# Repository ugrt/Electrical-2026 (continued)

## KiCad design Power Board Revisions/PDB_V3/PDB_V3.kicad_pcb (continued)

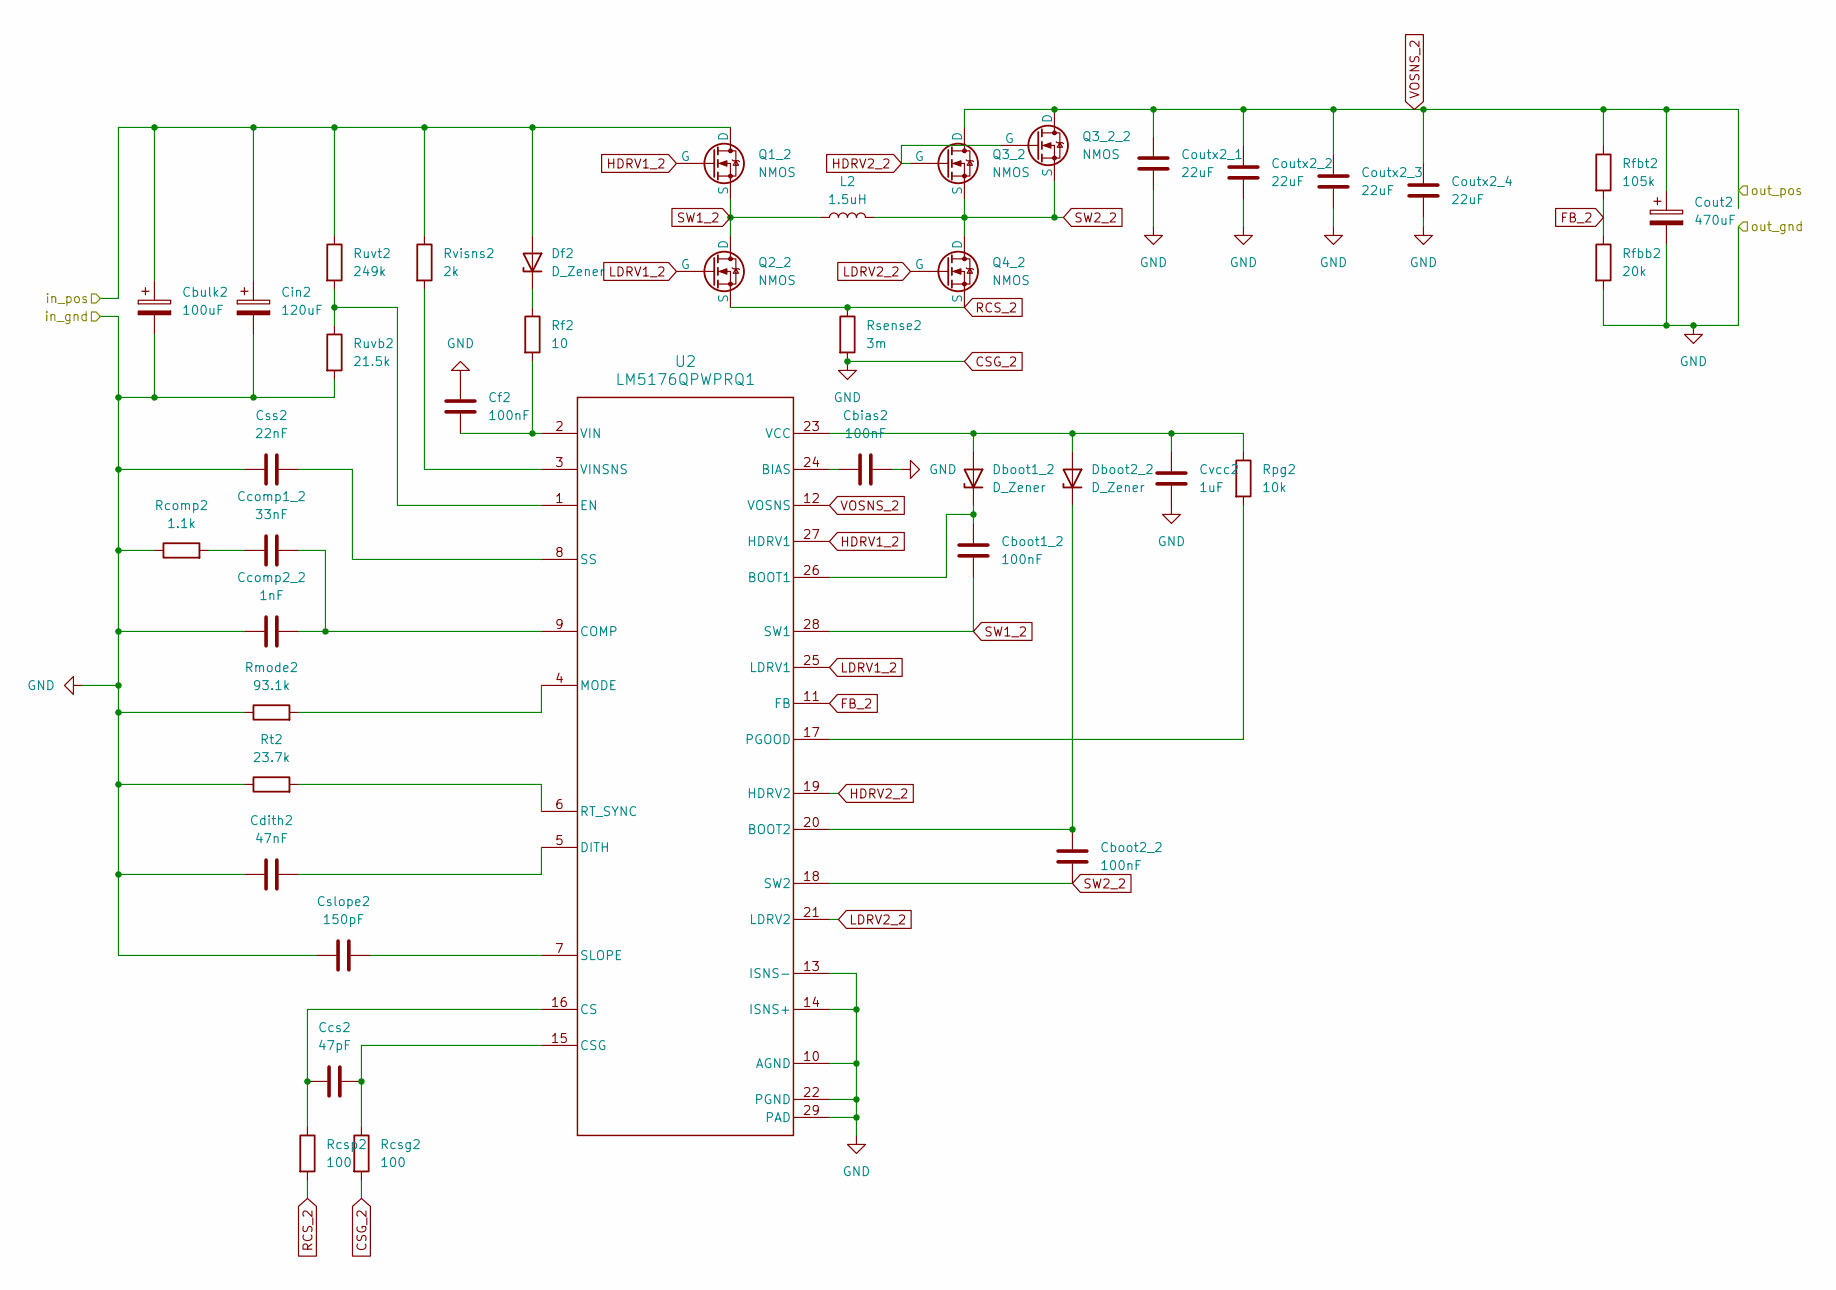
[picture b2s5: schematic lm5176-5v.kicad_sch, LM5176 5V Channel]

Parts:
Cbias2: 100nF; C_1206_3216Metric_Pad1.33x1.80mm_HandSolder; DigiKey_Part_Number 1276-3083-1-ND
Cboot1_2, Cboot2_2: 100nF; C_1206_3216Metric_Pad1.33x1.80mm_HandSolder; DigiKey_Part_Number 1276-3083-1-ND
Cbulk2: 100uF; CP_Radial_D10.0mm_P5.00mm; DigiKey_Part_Number P10343-ND
Ccomp1_2: 33nF; C_1206_3216Metric_Pad1.33x1.80mm_HandSolder; DigiKey_Part_Number 1276-3159-1-ND
Ccomp2_2: 1nF; C_1206_3216Metric_Pad1.33x1.80mm_HandSolder; DigiKey_Part_Number 1276-3070-1-ND
Ccs2: 47pF; C_1206_3216Metric_Pad1.33x1.80mm_HandSolder; DigiKey_Part_Number 1276-3270-1-ND
Cdith2: 47nF; C_1206_3216Metric_Pad1.33x1.80mm_HandSolder; DigiKey_Part_Number 1276-1149-1-ND
Cf2: 100nF; C_1206_3216Metric_Pad1.33x1.80mm_HandSolder; DigiKey_Part_Number KTS251B104K31N0T00
Cin2: 120uF; CP_Radial_D10.0mm_P5.00mm; DigiKey_Part_Number 10-EEU-FC1H121BCT-ND
Cout2: 470uF; CP_Radial_D10.0mm_P5.00mm; DigiKey_Part_Number 10-ECA-1HM471BCT-ND
Coutx2_1, Coutx2_2, Coutx2_3, Coutx2_4: 22uF; C_1206_3216Metric_Pad1.33x1.80mm_HandSolder; DigiKey_Part_Number 1276-3300-1-ND
Cslope2: 150pF; C_1206_3216Metric_Pad1.33x1.80mm_HandSolder; DigiKey_Part_Number 1276-CL31C151JHF1PNECT-ND
Css2: 22nF; C_1206_3216Metric_Pad1.33x1.80mm_HandSolder; DigiKey_Part_Number 1276-CL31B223KEFXPNECT-ND
Cvcc2: 1uF; C_1206_3216Metric_Pad1.33x1.80mm_HandSolder; DigiKey_Part_Number 1276-3093-1-ND
Dboot1_2, Dboot2_2: D_Zener; D_SOD-123F; DigiKey_Part_Number B260S1F-7DICT-ND
Df2: D_Zener; D_SOD-123F; DigiKey_Part_Number B260S1F-7DICT-ND
L2: 1.5uH; WE-HCM_1411
Q1_2, Q2_2, Q3_2, Q3_2_2, Q4_2: NMOS; IAUCN04S7L019
Rcomp2: 1.1k; R_1206_3216Metric_Pad1.30x1.75mm_HandSolder
Rcsg2: 100; R_1206_3216Metric_Pad1.30x1.75mm_HandSolder
Rcsp2: 100; R_1206_3216Metric_Pad1.30x1.75mm_HandSolder
Rf2: 10; R_1206_3216Metric_Pad1.30x1.75mm_HandSolder
Rfbb2: 20k; R_1206_3216Metric_Pad1.30x1.75mm_HandSolder
Rfbt2: 105k; R_1206_3216Metric_Pad1.30x1.75mm_HandSolder
Rmode2: 93.1k; R_1206_3216Metric_Pad1.30x1.75mm_HandSolder
Rpg2: 10k; R_1206_3216Metric_Pad1.30x1.75mm_HandSolder
Rsense2: 3m; WSLP2512-3L000
Rt2: 23.7k; R_1206_3216Metric_Pad1.30x1.75mm_HandSolder
Ruvb2: 21.5k; R_1206_3216Metric_Pad1.30x1.75mm_HandSolder
Ruvt2: 249k; R_1206_3216Metric_Pad1.30x1.75mm_HandSolder
Rvisns2: 2k; R_1206_3216Metric_Pad1.30x1.75mm_HandSolder
U2: LM5176QPWPRQ1; LM5176QPWPRQ1_N

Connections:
FB_2: Rfbb2.1, Rfbt2.2, U2.11 (FB)
GND: Cbias2.2, Cbulk2.2, Ccomp2_2.1, Cdith2.2, Cf2.1, Cin2.2, Cout2.2, Coutx2_1.2, Coutx2_2.2, Coutx2_3.2, Coutx2_4.2, Cslope2.1, Css2.1, Cvcc2.2, Rcomp2.1, Rcsg2.2, Rfbb2.2, Rmode2.1, Rsense2.2, Rt2.1, Ruvb2.2, U2.10 (AGND), U2.13 (ISNS-), U2.14 (ISNS+), U2.22 (PGND), U2.29 (PAD); also elsewhere on the board
HDRV1_2: Q1_2.2 (G), U2.27 (HDRV1)
HDRV2_2: Q3_2.2 (G), Q3_2_2.2 (G), U2.19 (HDRV2)
LDRV1_2: Q2_2.2 (G), U2.25 (LDRV1)
LDRV2_2: Q4_2.2 (G), U2.21 (LDRV2)
unnamed: Ccomp1_2.1, Rcomp2.2
unnamed: Cvcc2.1, Dboot1_2.2 (A), Dboot2_2.2 (A), Rpg2.1, U2.23 (VCC)
unnamed: Cboot1_2.1, Dboot1_2.1 (K), U2.26 (BOOT1)
unnamed: Cboot2_2.1, Dboot2_2.1 (K), U2.20 (BOOT2)
unnamed: Df2.1 (K), Rf2.1
unnamed: Cbias2.1, U2.24 (BIAS)
unnamed: Ccomp1_2.2, Ccomp2_2.2, U2.9 (COMP)
unnamed: Ccs2.1, Rcsp2.1, U2.16 (CS)
unnamed: Ccs2.2, Rcsg2.1, U2.15 (CSG)
unnamed: Cdith2.1, U2.5 (DITH)
unnamed: Ruvb2.1, Ruvt2.2, U2.1 (EN)
unnamed: Rmode2.2, U2.4 (MODE)
unnamed: Rpg2.2, U2.17 (PGOOD)
unnamed: Rt2.2, U2.6 (RT_SYNC)
unnamed: Cslope2.2, U2.7 (SLOPE)
unnamed: Css2.2, U2.8 (SS)
unnamed: Cf2.2, Rf2.2, U2.2 (VIN)
unnamed: Rvisns2.2, U2.3 (VINSNS)
RCS_2: Q2_2.3 (S), Q4_2.3 (S), Rcsp2.2, Rsense2.1
SW1_2: Cboot1_2.2, L2.1, Q1_2.3 (S), Q2_2.1 (D), U2.28 (SW1)
SW2_2: Cboot2_2.2, L2.2, Q3_2.3 (S), Q3_2_2.3 (S), Q4_2.1 (D), U2.18 (SW2)
VCC: Cbulk2.1, Cin2.1, Df2.2 (A), Q1_2.1 (D), Ruvt2.1, Rvisns2.1; also elsewhere on the board
VOSNS_2: Cout2.1, Coutx2_1.1, Coutx2_2.1, Coutx2_3.1, Coutx2_4.1, Q3_2.1 (D), Q3_2_2.1 (D), Rfbt2.1, U2.12 (VOSNS); also elsewhere on the board

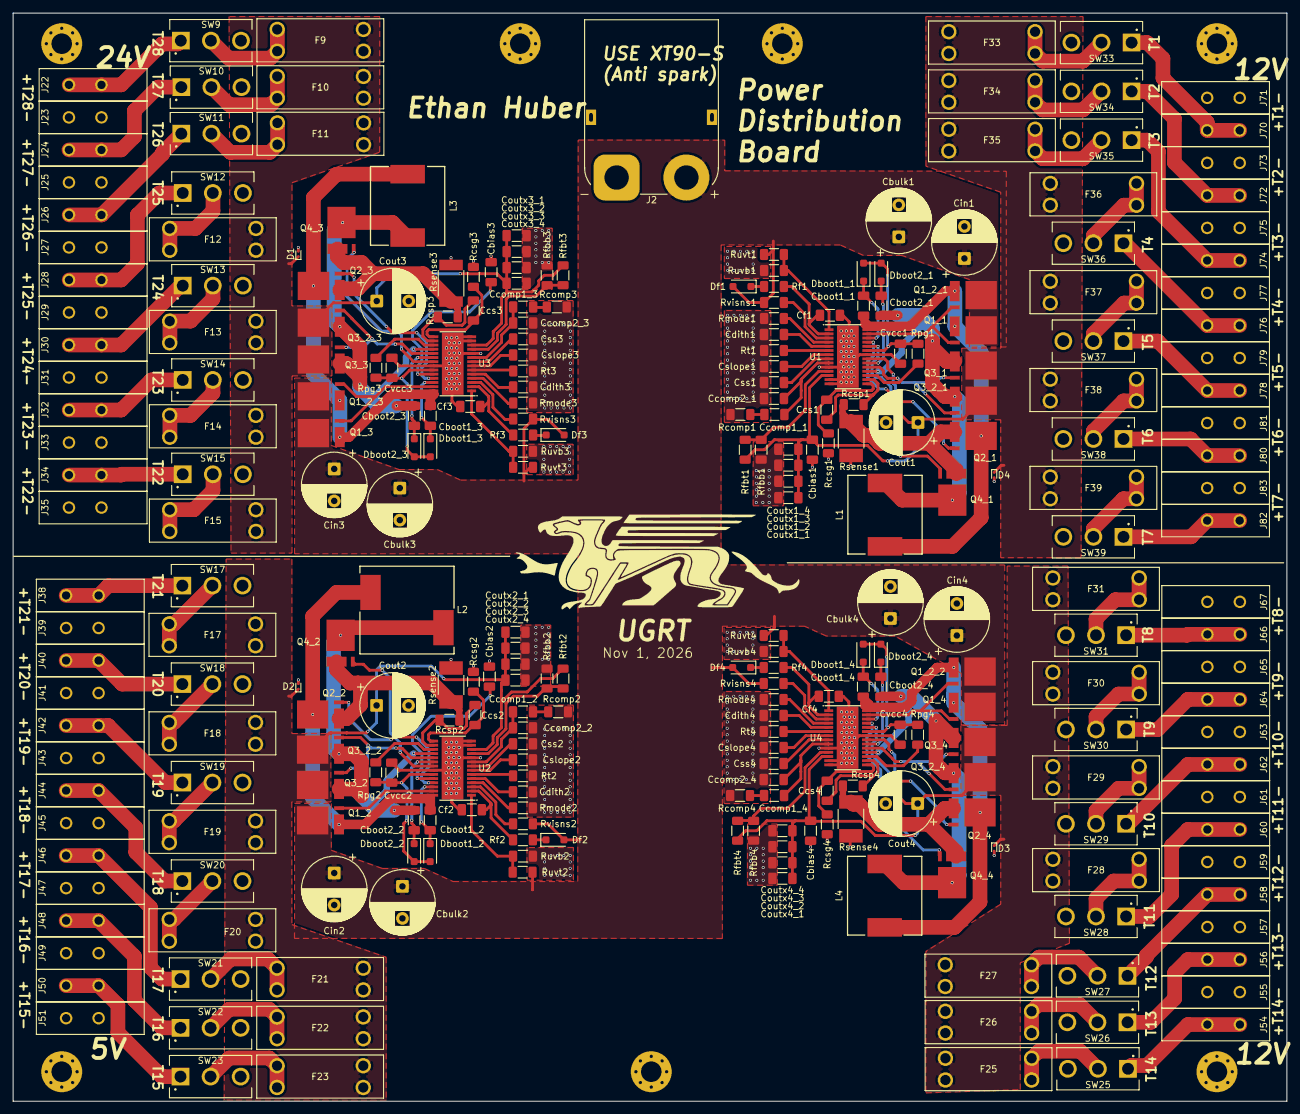
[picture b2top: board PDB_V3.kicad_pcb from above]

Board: 2 copper layers, 199.0 x 170.0 mm, 291 parts (0 on the bottom side), 164 nets.

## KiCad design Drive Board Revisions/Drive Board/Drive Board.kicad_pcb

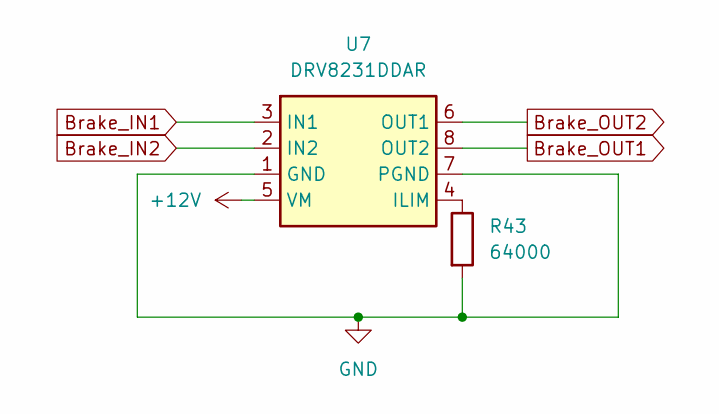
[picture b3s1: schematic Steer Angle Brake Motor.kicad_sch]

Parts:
R43: 64000; R_0603_1608Metric_Pad0.98x0.95mm_HandSolder
U7: DRV8231DDAR; Texas_HTSOP-8-1EP_3.9x4.9mm_P1.27mm_EP2.95x4.9mm_Mask2.4x3.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

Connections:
+12V: U7.5 (VM); also elsewhere on the board
Brake_IN1: U7.3 (IN1); also elsewhere on the board
Brake_IN2: U7.2 (IN2); also elsewhere on the board
Brake_OUT1: U7.8 (OUT2); also elsewhere on the board
Brake_OUT2: U7.6 (OUT1); also elsewhere on the board
GND: R43.2, U7.1 (GND), U7.7 (PGND); also elsewhere on the board
unnamed: R43.1, U7.4 (ILIM)

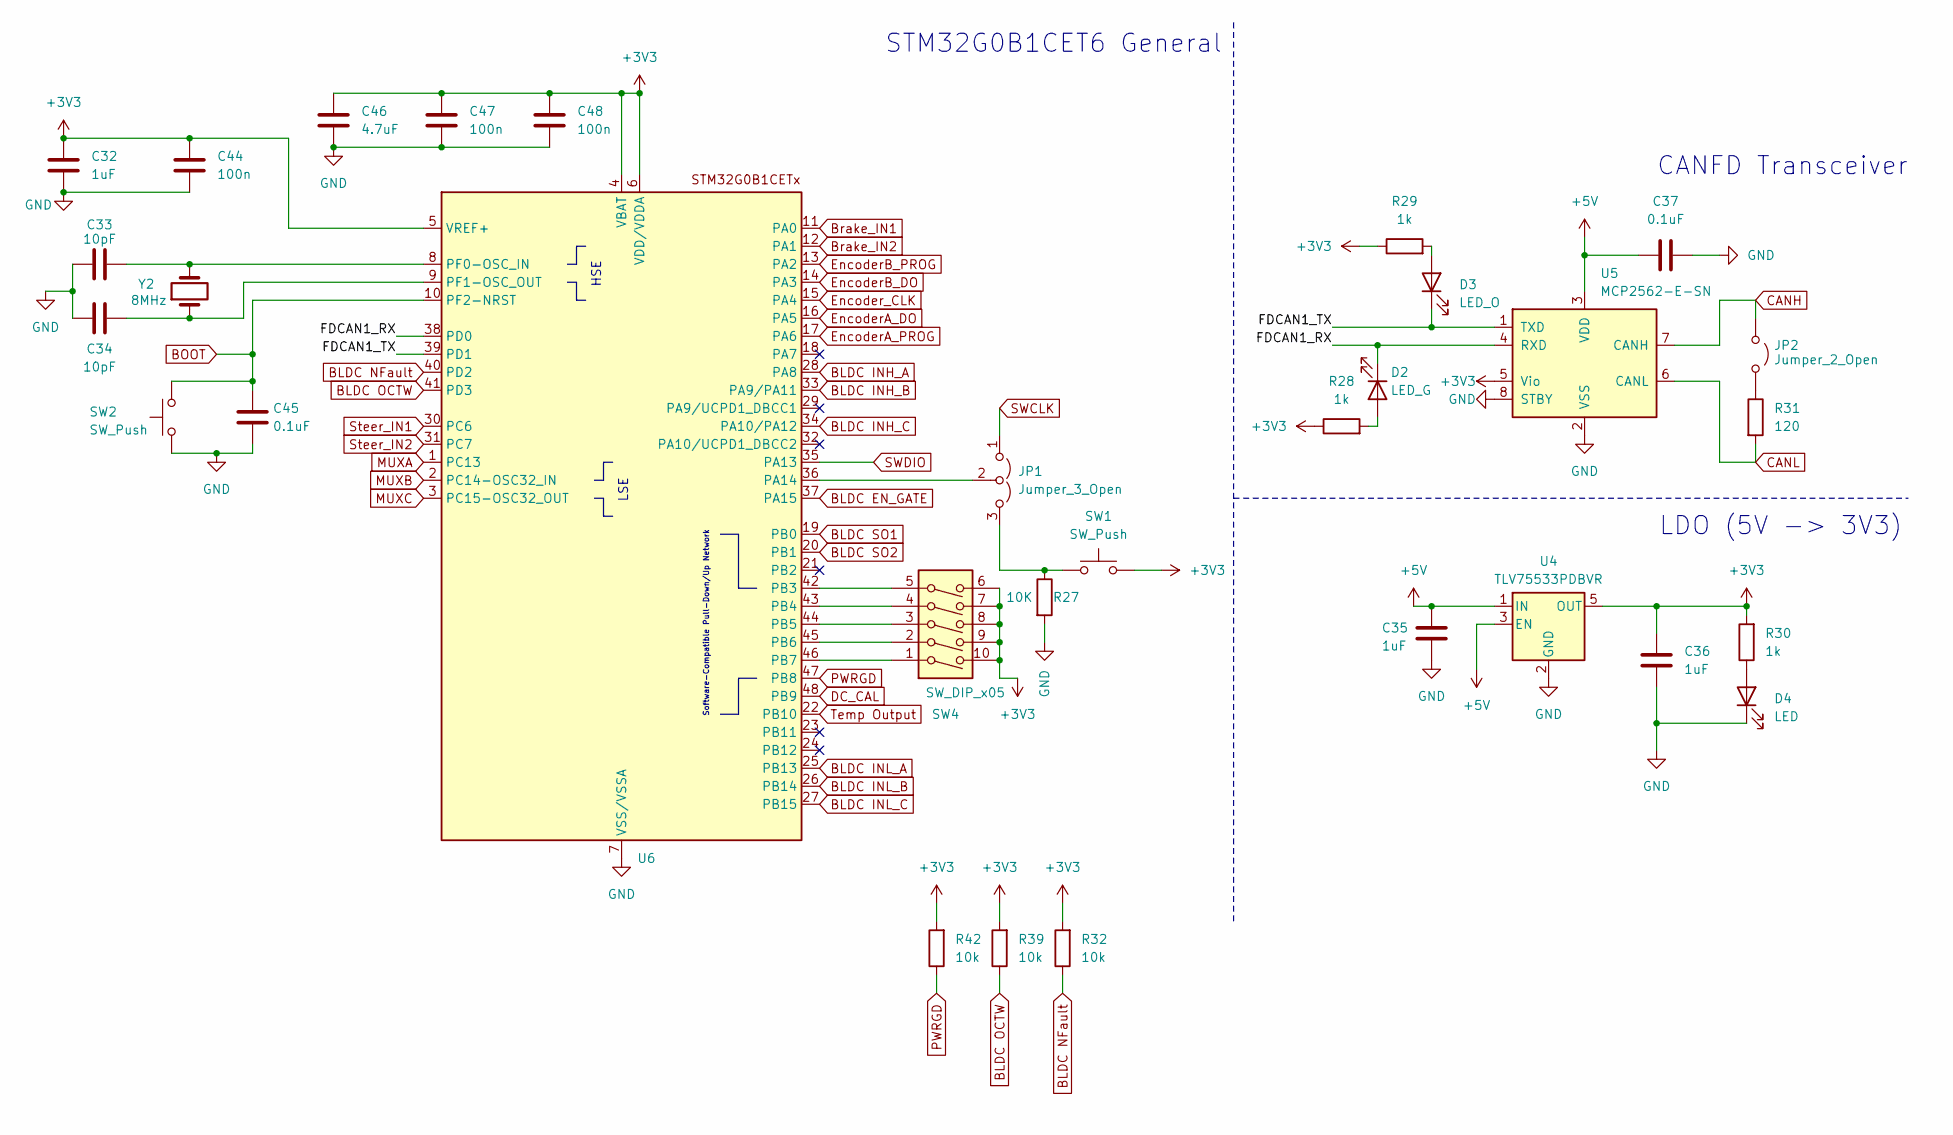
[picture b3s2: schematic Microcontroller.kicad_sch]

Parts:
C32, C35, C36: 1uF; C_0603_1608Metric_Pad1.08x0.95mm_HandSolder
C33, C34: 10pF; C_0603_1608Metric_Pad1.08x0.95mm_HandSolder
C37, C45: 0.1uF; C_0603_1608Metric_Pad1.08x0.95mm_HandSolder
C44, C47, C48: 100n; C_0603_1608Metric_Pad1.08x0.95mm_HandSolder
C46: 4.7uF; C_0603_1608Metric_Pad1.08x0.95mm_HandSolder
D2: LED_G; LED_0805_2012Metric_Pad1.15x1.40mm_HandSolder
D3: LED_O; LED_0805_2012Metric_Pad1.15x1.40mm_HandSolder
D4: LED; LED_0805_2012Metric_Pad1.15x1.40mm_HandSolder
JP1: Jumper_3_Open; PinHeader_1x03_P2.54mm_Vertical
JP2: Jumper_2_Open; PinHeader_1x02_P2.54mm_Vertical
R27: 10K; R_0603_1608Metric_Pad0.98x0.95mm_HandSolder
R28, R29, R30: 1k; R_0603_1608Metric_Pad0.98x0.95mm_HandSolder
R31: 120; R_0603_1608Metric_Pad0.98x0.95mm_HandSolder
R32, R39, R42: 10k; R_0603_1608Metric_Pad0.98x0.95mm_HandSolder
SW1, SW2: SW_Push; SKRPADE010_AAL
SW4: SW_DIP_x05; SW5_219SMT
U4: TLV75533PDBVR; SOT-23-5
U5: MCP2562-E-SN; SOIC-8_3.9x4.9mm_P1.27mm
U6: LQFP-48_7x7mm_P0.5mm
Y2: 8MHz; XTAL_ECS-80-8-30Q-VS-TR

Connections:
+3V3: C32.1, C36.1, C44.1, C46.1, C47.1, C48.1, R28.1, R29.1, R30.2, R32.2, R39.2, R42.2, SW1.2, SW4.6, SW4.7, SW4.8, SW4.9, SW4.10, U4.5 (OUT), U5.5 (Vio), U6.4 (VBAT), U6.5 (VREF+), U6.6 (VDD/VDDA); also elsewhere on the board
+5V: C35.1, C37.1, U4.1 (IN), U4.3 (EN), U5.3 (VDD); also elsewhere on the board
/Microcontroller/FDCAN1_RX: D2.1 (K), U5.4 (RXD), U6.38 (PD0)
/Microcontroller/FDCAN1_TX: D3.1 (K), U5.1 (TXD), U6.39 (PD1)
BLDC EN_GATE: U6.37 (PA15); also elsewhere on the board
BLDC INH_A: U6.28 (PA8); also elsewhere on the board
BLDC INH_B: U6.33 (PA9/PA11); also elsewhere on the board
BLDC INH_C: U6.34 (PA10/PA12); also elsewhere on the board
BLDC INL_A: U6.25 (PB13); also elsewhere on the board
BLDC INL_B: U6.26 (PB14); also elsewhere on the board
BLDC INL_C: U6.27 (PB15); also elsewhere on the board
BLDC NFault: R32.1, U6.40 (PD2); also elsewhere on the board
BLDC OCTW: R39.1, U6.41 (PD3); also elsewhere on the board
BLDC SO1: U6.19 (PB0); also elsewhere on the board
BLDC SO2: U6.20 (PB1); also elsewhere on the board
BOOT: C45.1, SW2.2, U6.10 (PF2-NRST); also elsewhere on the board
Brake_IN1: U6.11 (PA0); also elsewhere on the board
Brake_IN2: U6.12 (PA1); also elsewhere on the board
CANH: JP2.1 (A), U5.7 (CANH); also elsewhere on the board
CANL: R31.2, U5.6 (CANL); also elsewhere on the board
DC_CAL: U6.48 (PB9); also elsewhere on the board
EncoderA_DO: U6.16 (PA5); also elsewhere on the board
EncoderA_PROG: U6.17 (PA6); also elsewhere on the board
EncoderB_DO: U6.14 (PA3); also elsewhere on the board
EncoderB_PROG: U6.13 (PA2); also elsewhere on the board
Encoder_CLK: U6.15 (PA4); also elsewhere on the board
GND: C32.2, C33.1, C34.2, C35.2, C36.2, C37.2, C44.2, C45.2, C46.2, C47.2, C48.2, D4.1 (K), R27.2, SW2.1, U4.2 (GND), U5.2 (VSS), U5.8 (STBY), U6.7 (VSS/VSSA); also elsewhere on the board
MUXA: U6.1 (PC13); also elsewhere on the board
MUXB: U6.2 (PC14-OSC32_IN); also elsewhere on the board
MUXC: U6.3 (PC15-OSC32_OUT); also elsewhere on the board
unnamed: D2.2 (A), R28.2
unnamed: D3.2 (A), R29.2
unnamed: D4.2 (A), R30.1
unnamed: JP1.3 (B), R27.1, SW1.1
unnamed: JP1.2 (C), U6.36 (PA14)
unnamed: JP2.2 (B), R31.1
unnamed: SW4.5, U6.42 (PB3)
unnamed: SW4.4, U6.43 (PB4)
unnamed: SW4.3, U6.44 (PB5)
unnamed: SW4.2, U6.45 (PB6)
unnamed: SW4.1, U6.46 (PB7)
unnamed: C33.2, U6.8 (PF0-OSC_IN), Y2.2
unnamed: C34.1, U6.9 (PF1-OSC_OUT), Y2.1
PWRGD: R42.1, U6.47 (PB8); also elsewhere on the board
SWCLK: JP1.1 (A); also elsewhere on the board
SWDIO: U6.35 (PA13); also elsewhere on the board
Steer_IN1: U6.30 (PC6); also elsewhere on the board
Steer_IN2: U6.31 (PC7); also elsewhere on the board
Temp Output: U6.22 (PB10); also elsewhere on the board

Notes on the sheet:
LDO (5V -> 3V3)
CANFD Transceiver
Software-Compatible Pull-Down/Up Network
LSE
STM32G0B1CET6 General
HSE

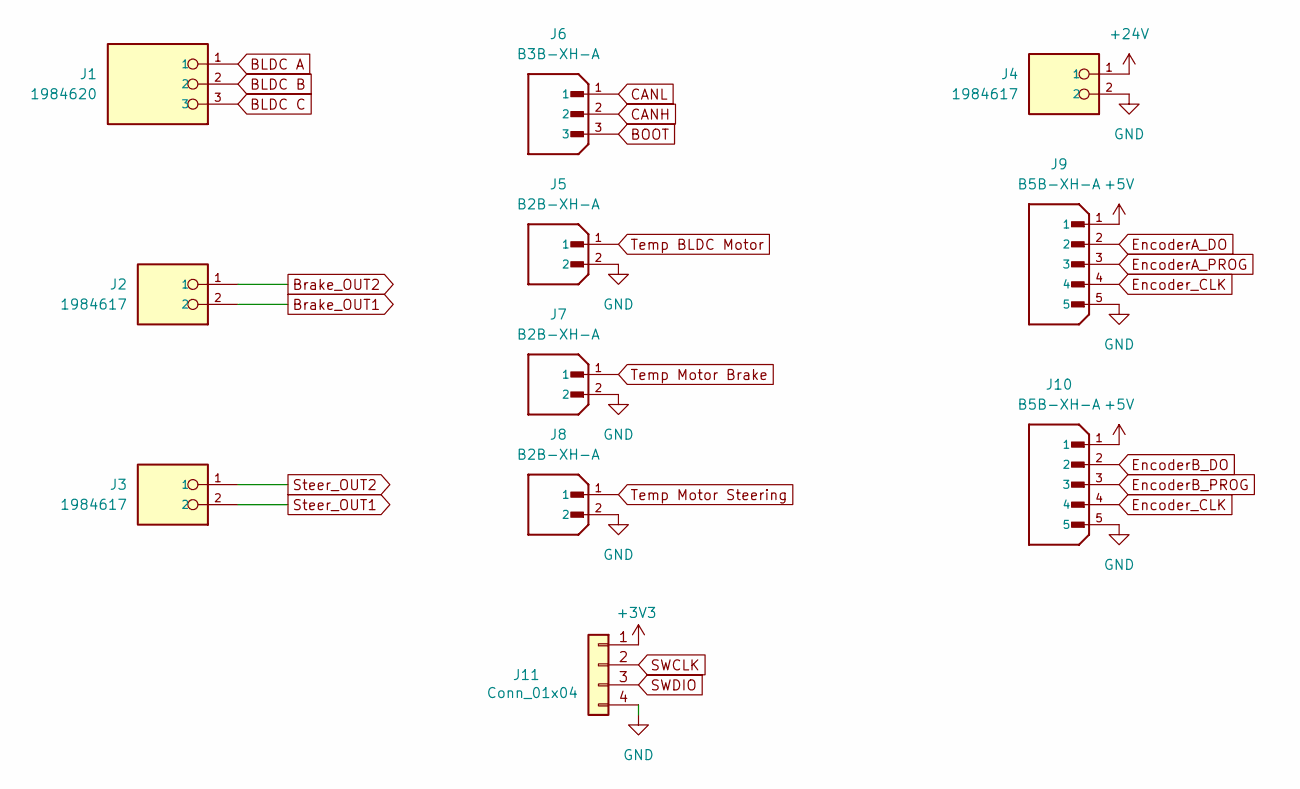
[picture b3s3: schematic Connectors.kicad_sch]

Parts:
J1: 1984620; PHOENIX_1984620
J2, J3, J4: 1984617; PHOENIX_1984617; PARTREV 22.08.2018
J5, J7, J8: B2B-XH-A; JST_B2B-XH-A; PARTREV N/A
J6: B3B-XH-A; JST_B3B-XH-A; PARTREV 7/4/21
J9, J10: B5B-XH-A; JST_B5B-XH-A; PARTREV 7/4/21
J11: Conn_01x04; PinHeader_1x04_P2.54mm_Vertical

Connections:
+3V3: J11.1; also elsewhere on the board
+5V: J9.1, J10.1; also elsewhere on the board
+24V: J4.1; also elsewhere on the board
BLDC A: J1.1; also elsewhere on the board
BLDC B: J1.2; also elsewhere on the board
BLDC C: J1.3; also elsewhere on the board
BOOT: J6.3; also elsewhere on the board
Brake_OUT1: J2.2; also elsewhere on the board
Brake_OUT2: J2.1; also elsewhere on the board
CANH: J6.2; also elsewhere on the board
CANL: J6.1; also elsewhere on the board
EncoderA_DO: J9.2; also elsewhere on the board
EncoderA_PROG: J9.3; also elsewhere on the board
EncoderB_DO: J10.2; also elsewhere on the board
EncoderB_PROG: J10.3; also elsewhere on the board
Encoder_CLK: J9.4, J10.4; also elsewhere on the board
GND: J4.2, J5.2, J7.2, J8.2, J9.5, J10.5, J11.4; also elsewhere on the board
SWCLK: J11.2; also elsewhere on the board
SWDIO: J11.3; also elsewhere on the board
Steer_OUT1: J3.2; also elsewhere on the board
Steer_OUT2: J3.1; also elsewhere on the board
Temp BLDC Motor: J5.1; also elsewhere on the board
Temp Motor Brake: J7.1; also elsewhere on the board
Temp Motor Steering: J8.1; also elsewhere on the board

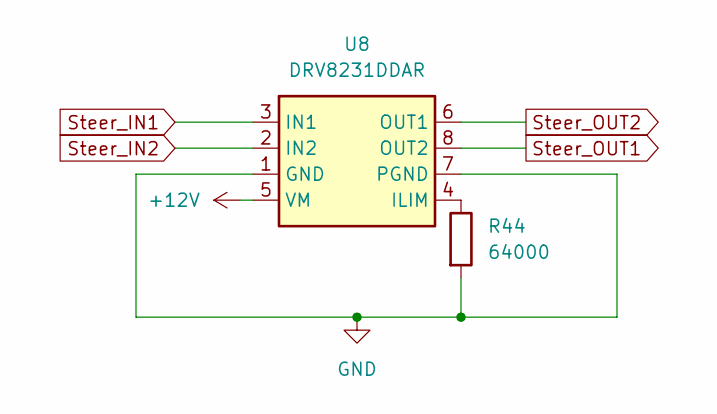
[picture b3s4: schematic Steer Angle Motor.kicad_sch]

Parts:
R44: 64000; R_0603_1608Metric_Pad0.98x0.95mm_HandSolder
U8: DRV8231DDAR; Texas_HTSOP-8-1EP_3.9x4.9mm_P1.27mm_EP2.95x4.9mm_Mask2.4x3.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

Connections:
+12V: U8.5 (VM); also elsewhere on the board
GND: R44.2, U8.1 (GND), U8.7 (PGND); also elsewhere on the board
unnamed: R44.1, U8.4 (ILIM)
Steer_IN1: U8.3 (IN1); also elsewhere on the board
Steer_IN2: U8.2 (IN2); also elsewhere on the board
Steer_OUT1: U8.8 (OUT2); also elsewhere on the board
Steer_OUT2: U8.6 (OUT1); also elsewhere on the board

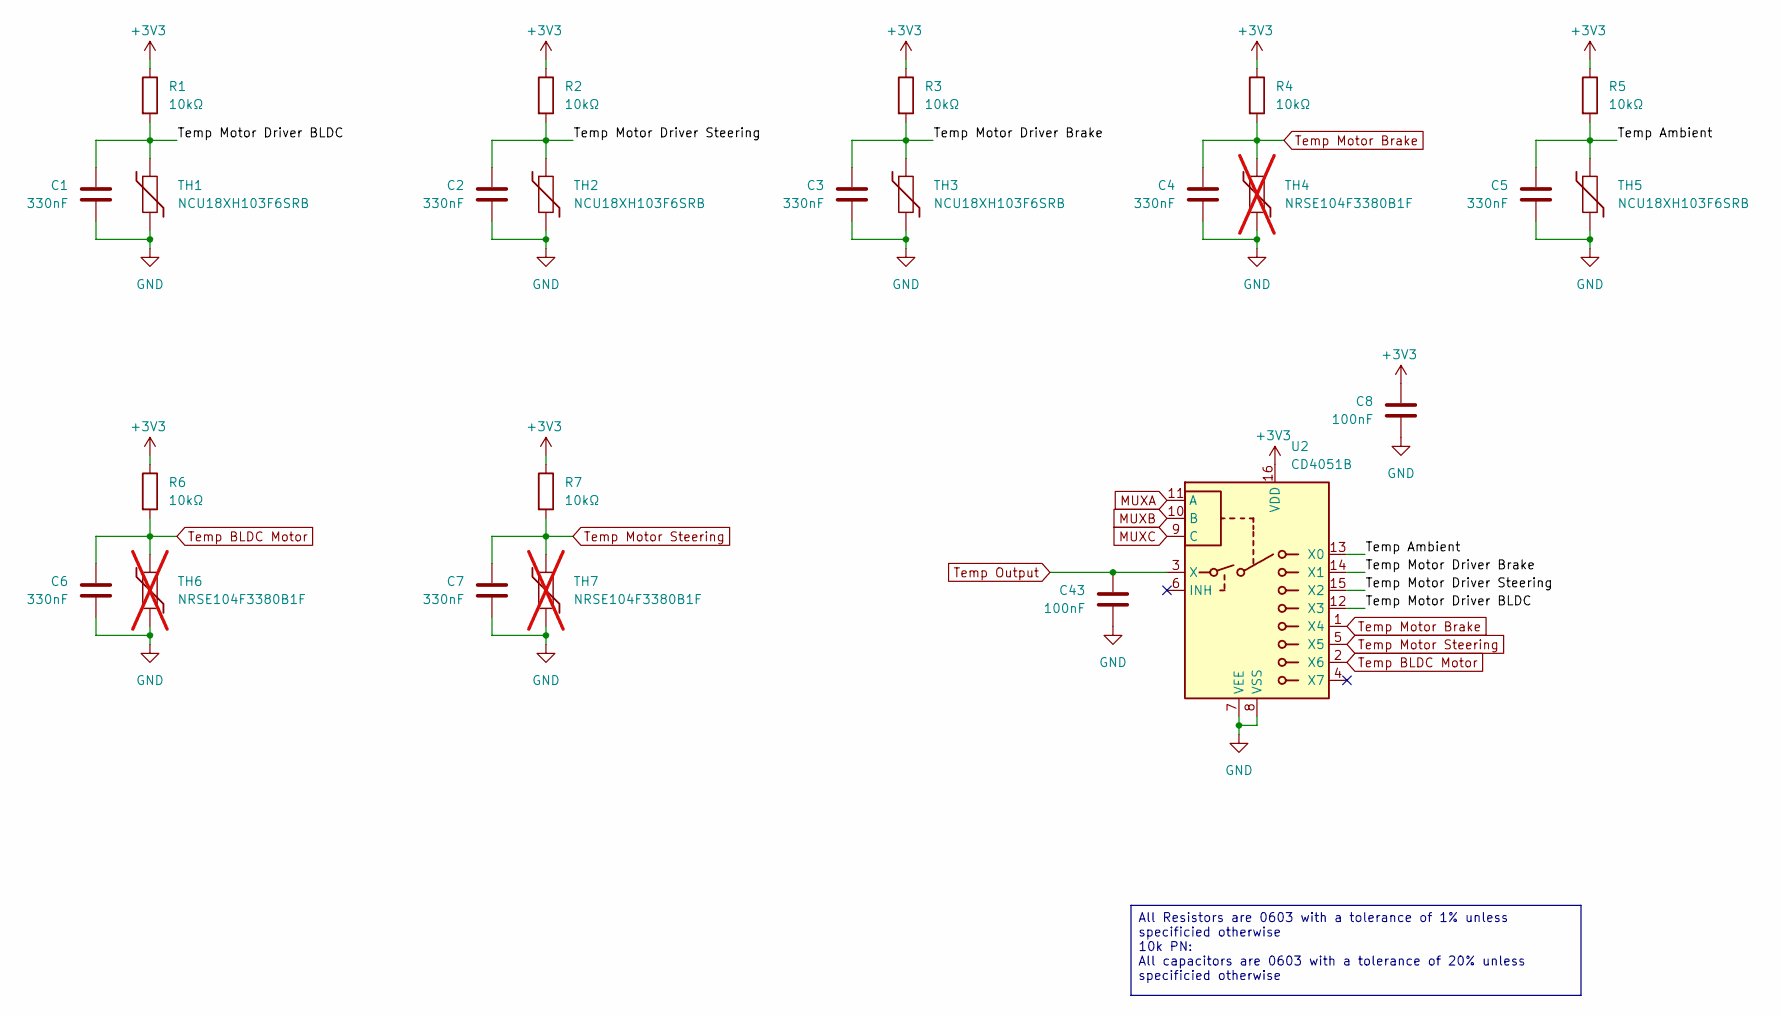
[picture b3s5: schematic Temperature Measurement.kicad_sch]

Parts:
C1, C2, C3, C4, C5, C6, C7: 330nF; C_0603_1608Metric_Pad1.08x0.95mm_HandSolder
C8, C43: 100nF; C_0603_1608Metric_Pad1.08x0.95mm_HandSolder
R1, R2, R3, R4, R5, R6, R7: 10kΩ; R_0603_1608Metric_Pad0.98x0.95mm_HandSolder
TH1, TH2, TH3, TH5: NCU18XH103F6SRB; R_0603_1608Metric_Pad0.98x0.95mm_HandSolder
TH4, TH6, TH7: NRSE104F3380B1F; not fitted
U2: CD4051B; TSSOP-16_4.4x5mm_P0.65mm

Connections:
+3V3: C8.1, R1.1, R2.1, R3.1, R4.1, R5.1, R6.1, R7.1, U2.16 (VDD); also elsewhere on the board
/Temperature Measurement/Temp Ambient: C5.1, R5.2, TH5.1, U2.13 (X0)
/Temperature Measurement/Temp Motor Driver BLDC: C1.1, R1.2, TH1.1, U2.12 (X3)
/Temperature Measurement/Temp Motor Driver Brake: C3.1, R3.2, TH3.1, U2.14 (X1)
/Temperature Measurement/Temp Motor Driver Steering: C2.1, R2.2, TH2.1, U2.15 (X2)
GND: C1.2, C2.2, C3.2, C4.2, C5.2, C6.2, C7.2, C8.2, C43.2, TH1.2, TH2.2, TH3.2, TH4.2, TH5.2, TH6.2, TH7.2, U2.7 (VEE), U2.8 (VSS); also elsewhere on the board
MUXA: U2.11 (A); also elsewhere on the board
MUXB: U2.10 (B); also elsewhere on the board
MUXC: U2.9 (C); also elsewhere on the board
Temp BLDC Motor: C6.1, R6.2, TH6.1, U2.2 (X6); also elsewhere on the board
Temp Motor Brake: C4.1, R4.2, TH4.1, U2.1 (X4); also elsewhere on the board
Temp Motor Steering: C7.1, R7.2, TH7.1, U2.5 (X5); also elsewhere on the board
Temp Output: C43.1, U2.3 (X); also elsewhere on the board

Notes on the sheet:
All Resistors are 0603 with a tolerance of 1% unless specificied otherwise 10k PN: All capacitors are 0603 with a tolerance of 20% unless specificied otherwise

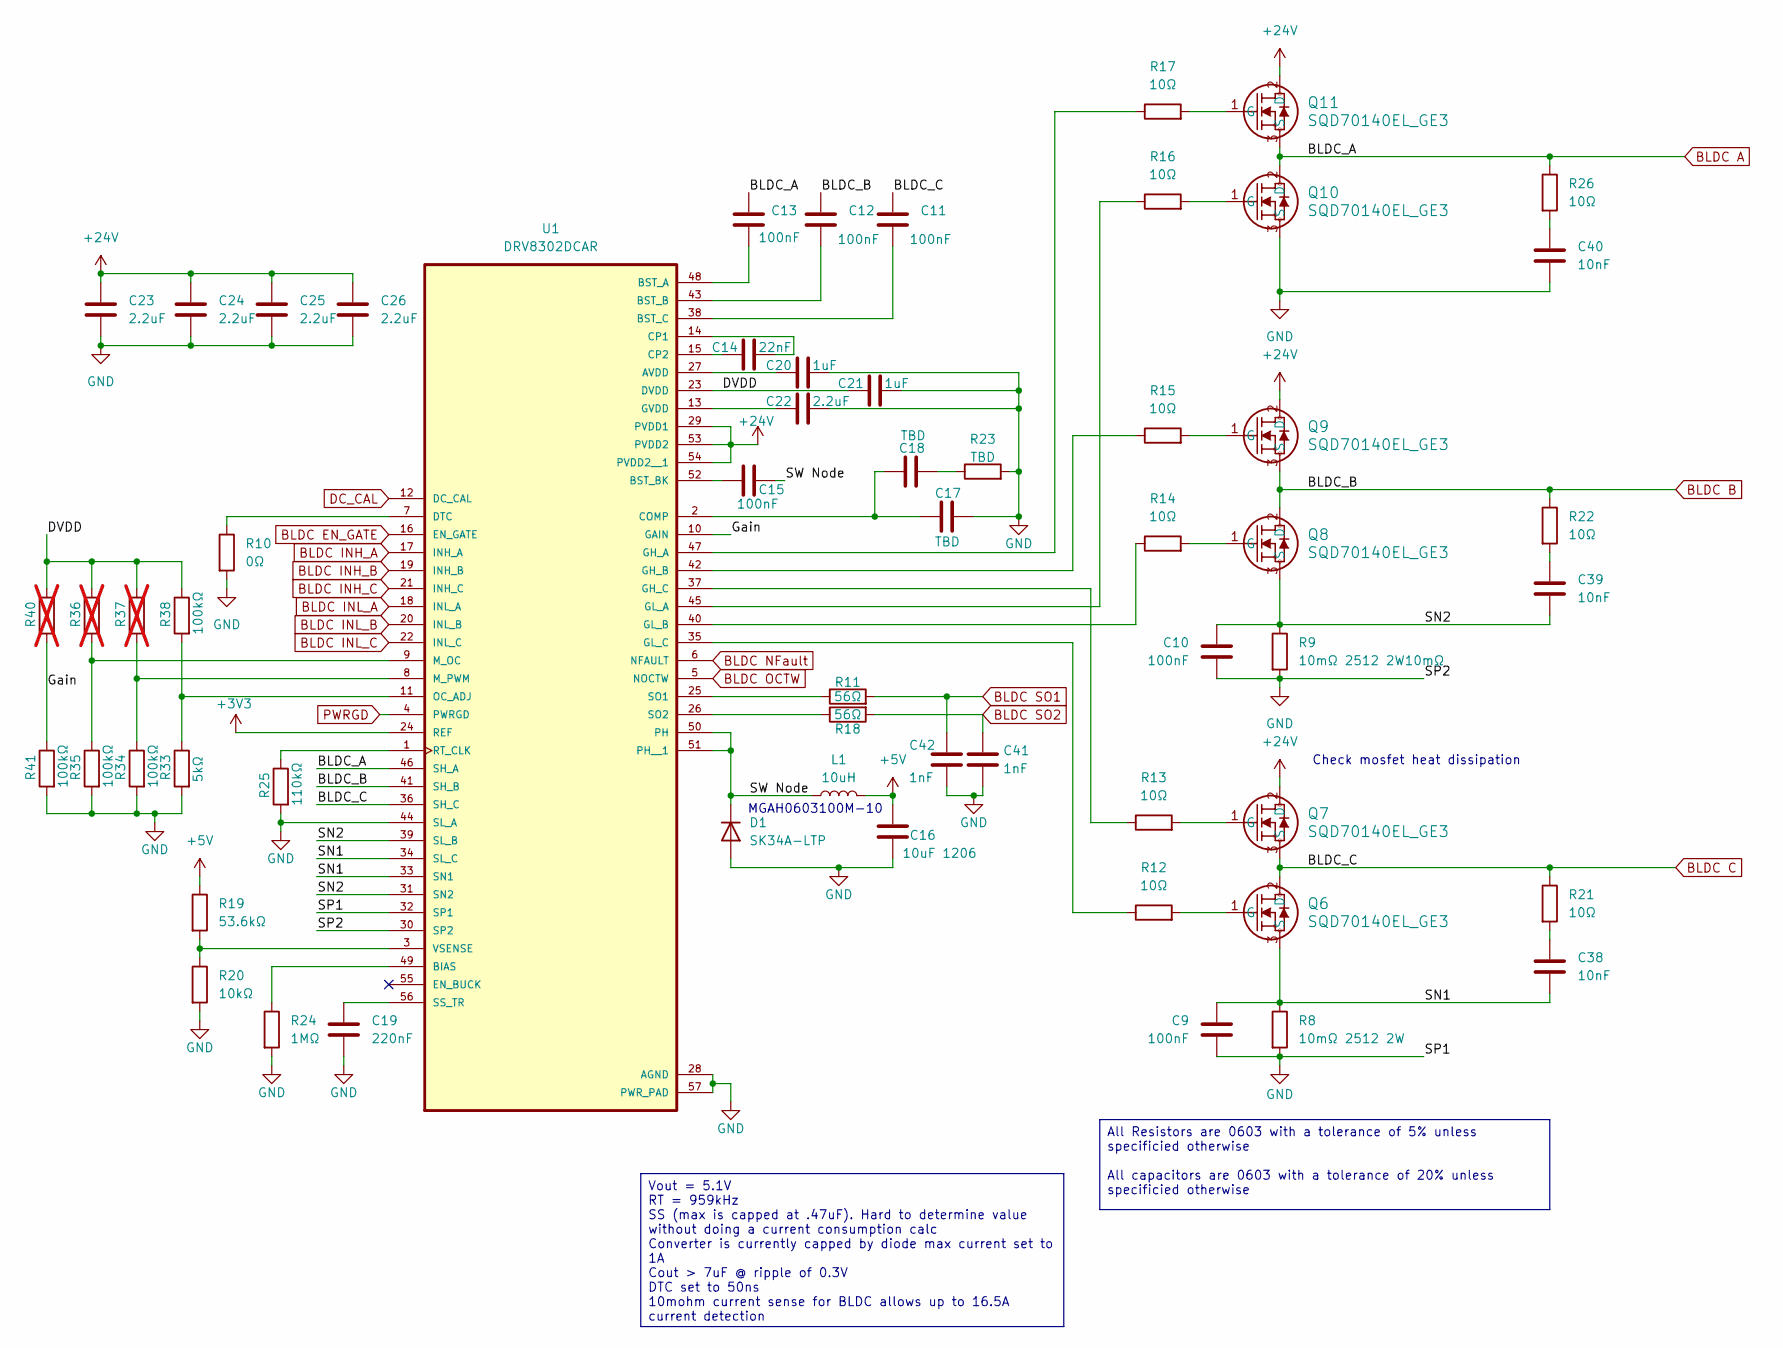
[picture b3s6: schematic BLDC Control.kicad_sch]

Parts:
C9, C10, C11, C12, C13, C15: 100nF; C_0603_1608Metric_Pad1.08x0.95mm_HandSolder
C14: 22nF; C_0603_1608Metric_Pad1.08x0.95mm_HandSolder
C16: 10uF 1206; C_1206_3216Metric_Pad1.33x1.80mm_HandSolder
C17, C18: TBD; C_0603_1608Metric_Pad1.08x0.95mm_HandSolder
C19: 220nF; C_0603_1608Metric_Pad1.08x0.95mm_HandSolder
C20, C21: 1uF; C_0603_1608Metric_Pad1.08x0.95mm_HandSolder
C22, C23, C24, C25, C26: 2.2uF; C_0603_1608Metric_Pad1.08x0.95mm_HandSolder
C38, C39, C40: 10nF; C_0603_1608Metric_Pad1.08x0.95mm_HandSolder
C41, C42: 1nF; C_0603_1608Metric_Pad1.08x0.95mm_HandSolder
D1: SK34A-LTP; SMADO-214AC_MCC-L
L1: 10uH; IND_MGAH0603_LRD
Q6, Q7, Q8, Q9, Q10, Q11: SQD70140EL_GE3; TO_40EL_GE3_VIS
R8: 10mΩ 2512 2W; R_2512_6332Metric_Pad1.40x3.35mm_HandSolder
R9: 10mΩ 2512 2W10mΩ; R_2512_6332Metric_Pad1.40x3.35mm_HandSolder
R10: 0Ω; R_0603_1608Metric_Pad0.98x0.95mm_HandSolder
R11, R18: 56Ω; R_0603_1608Metric_Pad0.98x0.95mm_HandSolder
R12, R13, R14, R15, R16, R17, R21, R22, R26: 10Ω; R_0603_1608Metric_Pad0.98x0.95mm_HandSolder
R19: 53.6kΩ; R_0603_1608Metric_Pad0.98x0.95mm_HandSolder
R20: 10kΩ; R_0603_1608Metric_Pad0.98x0.95mm_HandSolder
R23: TBD; R_0603_1608Metric_Pad0.98x0.95mm_HandSolder
R24: 1MΩ; R_0603_1608Metric_Pad0.98x0.95mm_HandSolder
R25: 110kΩ; R_0603_1608Metric_Pad0.98x0.95mm_HandSolder
R33: 5kΩ; R_0603_1608Metric_Pad0.98x0.95mm_HandSolder
R34, R35, R38, R41: 100kΩ; R_0603_1608Metric_Pad0.98x0.95mm_HandSolder
R36, R37, R40: R_0603_1608Metric_Pad0.98x0.95mm_HandSolder; not fitted
U1: DRV8302DCAR; SOP50P810X120-57N

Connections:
+3V3: U1.24 (REF); also elsewhere on the board
+5V: C16.1, L1.2, R19.1; also elsewhere on the board
+24V: C23.1, C24.1, C25.1, C26.1, Q7.2 (D), Q9.2 (D), Q11.2 (D), U1.29 (PVDD1), U1.53 (PVDD2), U1.54 (PVDD2__1); also elsewhere on the board
/BLDC Control/DVDD: C21.1, R36.1, R37.1, R38.1, R40.1, U1.23 (DVDD)
/BLDC Control/Gain: R40.2, R41.1, U1.10 (GAIN)
/BLDC Control/SN1: C9.1, C38.2, Q6.3 (S), R8.1, U1.33 (SN1), U1.34 (SL_C)
/BLDC Control/SN2: C10.1, C39.2, Q8.3 (S), R9.1, U1.31 (SN2), U1.39 (SL_B)
/BLDC Control/SW Node: C15.2, D1.1 (K), L1.1, U1.50 (PH), U1.51 (PH__1)
BLDC A: C13.1, Q10.2 (D), Q11.3 (S), R26.1, U1.46 (SH_A); also elsewhere on the board
BLDC B: C12.1, Q8.2 (D), Q9.3 (S), R22.1, U1.41 (SH_B); also elsewhere on the board
BLDC C: C11.1, Q6.2 (D), Q7.3 (S), R21.1, U1.36 (SH_C); also elsewhere on the board
BLDC EN_GATE: U1.16 (EN_GATE); also elsewhere on the board
BLDC INH_A: U1.17 (INH_A); also elsewhere on the board
BLDC INH_B: U1.19 (INH_B); also elsewhere on the board
BLDC INH_C: U1.21 (INH_C); also elsewhere on the board
BLDC INL_A: U1.18 (INL_A); also elsewhere on the board
BLDC INL_B: U1.20 (INL_B); also elsewhere on the board
BLDC INL_C: U1.22 (INL_C); also elsewhere on the board
BLDC NFault: U1.6 (NFAULT); also elsewhere on the board
BLDC OCTW: U1.5 (NOCTW); also elsewhere on the board
BLDC SO1: C42.1, R11.2; also elsewhere on the board
BLDC SO2: C41.1, R18.2; also elsewhere on the board
DC_CAL: U1.12 (DC_CAL); also elsewhere on the board
GND: C9.2, C10.2, C16.2, C17.2, C19.2, C20.2, C21.2, C22.2, C23.2, C24.2, C25.2, C26.2, C40.2, C41.2, C42.2, D1.2 (A), Q10.3 (S), R8.2, R9.2, R10.2, R20.2, R23.2, R24.2, R25.2, R33.2, R34.2, R35.2, R41.2, U1.28 (AGND), U1.30 (SP2), U1.32 (SP1), U1.44 (SL_A), U1.57 (PWR_PAD); also elsewhere on the board
unnamed: C18.2, R23.1
unnamed: C38.1, R21.2
unnamed: C39.1, R22.2
unnamed: C40.1, R26.2
unnamed: Q6.1 (G), R12.2
unnamed: Q7.1 (G), R13.2
unnamed: Q8.1 (G), R14.2
unnamed: Q9.1 (G), R15.2
unnamed: Q10.1 (G), R16.2
unnamed: Q11.1 (G), R17.2
unnamed: C20.1, U1.27 (AVDD)
unnamed: R24.1, U1.49 (BIAS)
unnamed: C13.2, U1.48 (BST_A)
unnamed: C12.2, U1.43 (BST_B)
unnamed: C15.1, U1.52 (BST_BK)
unnamed: C11.2, U1.38 (BST_C)
unnamed: C17.1, C18.1, U1.2 (COMP)
unnamed: C14.2, U1.14 (CP1)
unnamed: C14.1, U1.15 (CP2)
unnamed: R10.1, U1.7 (DTC)
unnamed: R17.1, U1.47 (GH_A)
unnamed: R15.1, U1.42 (GH_B)
unnamed: R13.1, U1.37 (GH_C)
unnamed: R16.1, U1.45 (GL_A)
unnamed: R14.1, U1.40 (GL_B)
unnamed: R12.1, U1.35 (GL_C)
unnamed: C22.1, U1.13 (GVDD)
unnamed: R35.1, R36.2, U1.9 (M_OC)
unnamed: R34.1, R37.2, U1.8 (M_PWM)
unnamed: R33.1, R38.2, U1.11 (OC_ADJ)
unnamed: R25.1, U1.1 (RT_CLK)
unnamed: R11.1, U1.25 (SO1)
unnamed: R18.1, U1.26 (SO2)
unnamed: C19.1, U1.56 (SS_TR)
unnamed: R19.2, R20.1, U1.3 (VSENSE)
PWRGD: U1.4 (PWRGD); also elsewhere on the board

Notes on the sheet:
Check mosfet heat dissipation
MGAH0603100M-10
All Resistors are 0603 with a tolerance of 5% unless specificied otherwise All capacitors are 0603 with a tolerance of 20% unless specificied otherwise
Vout = 5.1V RT = 959kHz SS (max is capped at .47uF). Hard to determine value without doing a current consumption calc Converter is currently capped by diode max current set to 1A Cout > 7uF @ ripple of 0.3V DTC set to 50ns 10mohm current sense for BLDC allows up to 16.5A current detection

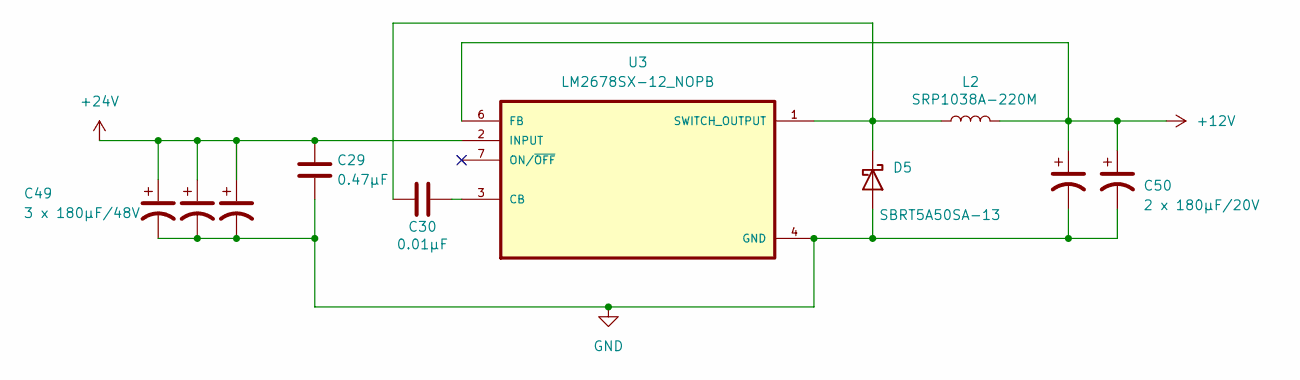
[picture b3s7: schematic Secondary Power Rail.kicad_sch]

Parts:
C27, C28: C_Polarized_US; CP_Elec_8x10.5
C29: 0.47μF; C_0603_1608Metric_Pad1.08x0.95mm_HandSolder
C30: 0.01μF; C_0603_1608Metric_Pad1.08x0.95mm_HandSolder
C31: 180μF/16V; CP_Elec_6.3x7.7
C49: 3 x 180μF/48V; CP_Elec_8x10.5
C50: 2 x 180μF/20V; CP_Elec_6.3x7.7
D5: SBRT5A50SA-13; SMA_DIO-L
L2: SRP1038A-220M; SRP1038A-220M_BRN
U3: LM2678SX-12_NOPB; TO-263-7_TabPin8

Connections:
+12V: C31.1, C50.1, L2.2, U3.6 (FB); also elsewhere on the board
+24V: C27.1, C28.1, C29.1, C49.1, U3.2 (INPUT); also elsewhere on the board
GND: C27.2, C28.2, C29.2, C31.2, C49.2, C50.2, D5.2 (A), U3.4 (GND); also elsewhere on the board
unnamed: C30.1, D5.1 (K), L2.1, U3.1 (SWITCH_OUTPUT)
unnamed: C30.2, U3.3 (CB)
